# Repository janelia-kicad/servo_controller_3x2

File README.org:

# Created 2018-11-28 Wed 14:32
#+OPTIONS: title:nil author:nil email:nil toc:t |:t ^:nil
* Repository Information

- Name :: servo_controller_3x2
- Version :: 1.0
- License :: Open-Source Hardware
- URL :: https://github.com/janelia-kicad/servo_controller_3x2
- Author :: Peter Polidoro
- Email :: peter@polidoro.io

** Description

This device independently controls up to 16 5V hobby servos.

* Images

* Schematic

[[file:./schematic/servo_controller_3x2.pdf][./schematic/servo_controller_3x2.pdf]]

[[file:./schematic/images/schematic00.png]]

[[file:./schematic/images/schematic01.png]]

* Gerbers

Send gerbers zip file to your favorite PCB manufacturer for fabrication.

[[file:./gerbers/servo_controller_3x2_v1.0.zip][./gerbers/servo_controller_3x2_v1.0.zip]]

[[file:./gerbers/images/gerbers00.png]]

[[file:./gerbers/images/gerbers01.png]]

* Bill of Materials

** PCB Parts

| Item | Reference(s)    | Quantity | PartNumber        | Vendor  | Description                                              |
|------+-----------------+----------+-------------------+---------+----------------------------------------------------------|
|    1 | C1              |        1 | PCE3812CT-ND      | digikey | CAP ALUM 220UF 20% 50V SMD                               |
|    2 | C2              |        1 | 399-13229-1-ND    | digikey | CAP CER 0.1UF 50V 10% X7R 1210                           |
|    3 | C3              |        1 | 445-4536-1-ND     | digikey | CAP CER 10UF 50V 10% X7S 1210                            |
|    4 | D1              |        1 | 568-11697-1-ND    | digikey | DIODE SCHOTTKY 45V 10A CFP15                             |
|    5 | L1              |        1 | 350-1722-ND       | digikey | LED 2MM 5V VERTICAL RED PC MNT                           |
|    6 | MDB1            |        2 | S1011E-16-ND      | digikey | 16 Position Header Through Hole Male Pins                |
|    7 | P1              |        1 | CP-063AH-ND       | digikey | CONN PWR JACK DC 2.1X5.5 8A T/H                          |
|    8 | P2              |        1 | SAM12360-ND       | digikey | TSW-116-07-L-T                                           |
|    9 | R1 R2           |        2 | YAG5470CT-ND      | digikey | RES SMD 4.7K OHM 1% 1/2W 1210                            |
|   10 | RP1 RP2 RP3 RP4 |        4 | 744C083221JPCT-ND | digikey | RES ARRAY 4 RES 220 OHM 2012                             |
|   11 | U1              |        1 | 568-5931-1-ND     | digikey | LED Driver IC 16 Output Linear PWM Dimming 25mA 28-TSSOP |

** Supplemental Parts

| Item | Quantity | PartNumber   | Vendor  | Description                       |
|------+----------+--------------+---------+-----------------------------------|
|    1 |        1 | 1939-1410-ND | digikey | 40W 5V 8A DESKTOP                 |
|    2 |        1 | 1939-1027-ND | digikey | CORD 18AWG 1-15P - 320-C7 6FT BLK |
|    3 |        4 | 1738-1255-ND | digikey | 9G METAL GEAR MICRO SERVO         |
|      |          |              |         |                                   |

** Vendor Parts Lists

[[file:./bom/digikey_parts.csv][./bom/digikey_parts.csv]]

[[file:./bom/supplemental_digikey_parts.csv][./bom/supplemental_digikey_parts.csv]]

* Supplemental Documentation

** Assembly Instructions

- Solder surface mount and through hole components onto the pcb.

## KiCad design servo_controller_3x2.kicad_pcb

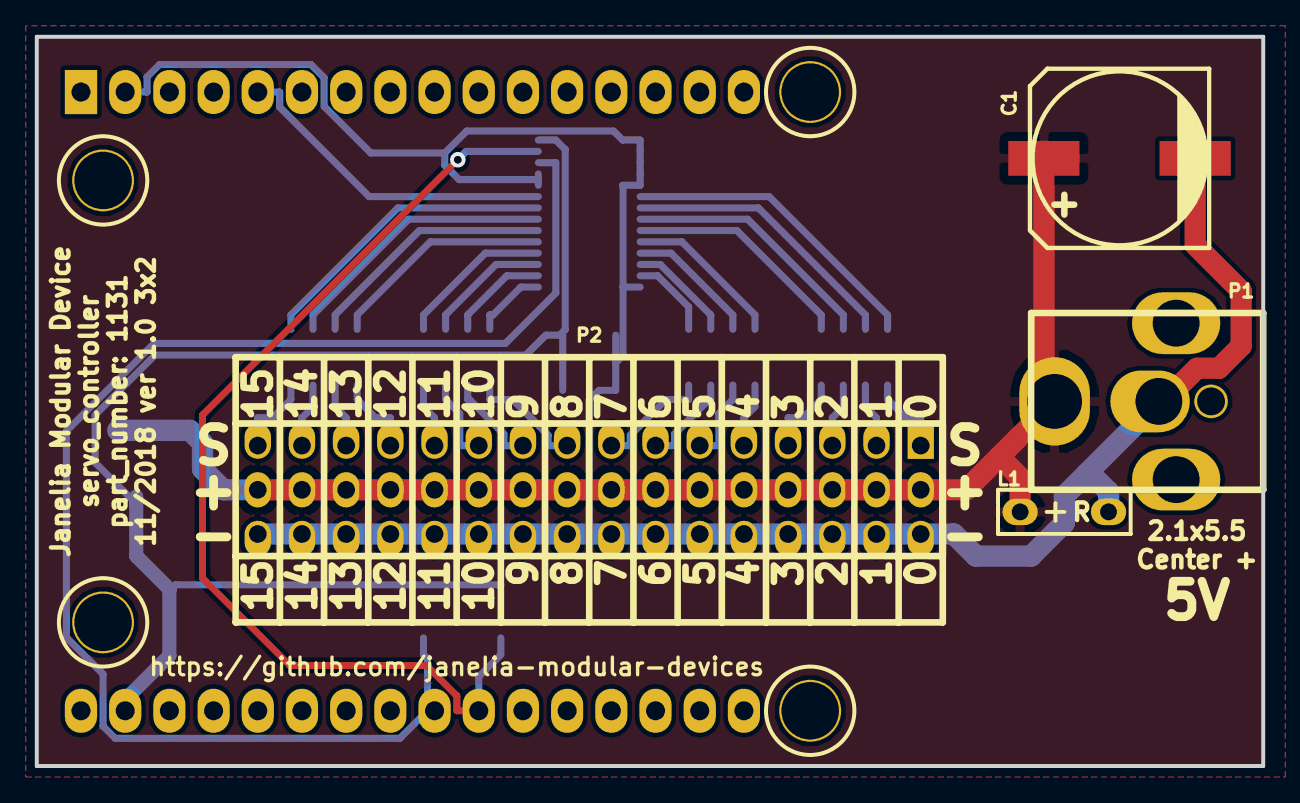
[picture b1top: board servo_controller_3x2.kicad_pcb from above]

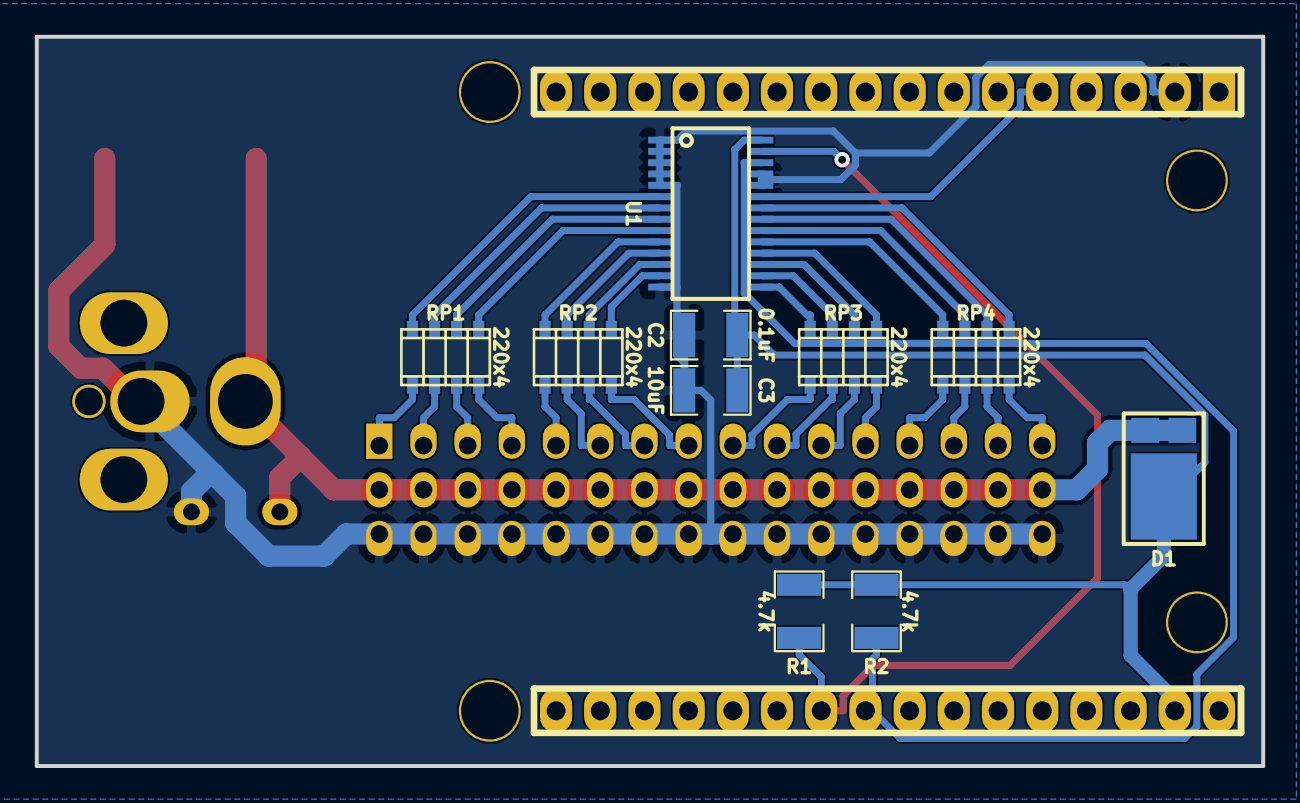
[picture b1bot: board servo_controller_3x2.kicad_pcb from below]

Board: 2 copper layers, 70.5 x 41.9 mm, 15 parts (10 on the bottom side), 38 nets.

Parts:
C1: 220uF_POL; C_ELEC_10
C2: 0.1uF; SM1210
C3: 10uF; SM1210
D1: diode_schottky_45V_10A; CFP15
L1: LED_5V_RED; LED_555-3XXX_R
MDB1: VAL**; MODULAR_DEVICE_BASE_3X2_MALE
P1: PWR_JACK_2.1x5.5; DCJACK_2PIN_HIGHCURRENT
P2: HEADER_03X16; HEADER_03x16
R1, R2: 4.7k; SM1210
RP1, RP2, RP3, RP4: 220x4; RESISTOR_PACK_SM1206x4
U1: PCA9685; TSSOP28

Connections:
/SCL: MDB1.19, R2.2, U1.26
/SDA: MDB1.18, R1.2, U1.27
/servo_3x2/PWM_0: RP1.7, U1.6
/servo_3x2/PWM_1: RP1.5, U1.7
/servo_3x2/PWM_2: RP1.3, U1.8
/servo_3x2/PWM_3: RP1.1, U1.9
/servo_3x2/PWM_4: RP2.7, U1.10
/servo_3x2/PWM_5: RP2.5, U1.11
/servo_3x2/PWM_6: RP2.3, U1.12
/servo_3x2/PWM_7: RP2.1, U1.13
/servo_3x2/PWM_8: RP3.7, U1.15
/servo_3x2/PWM_9: RP3.5, U1.16
/servo_3x2/PWM_10: RP3.3, U1.17
/servo_3x2/PWM_11: RP3.1, U1.18
/servo_3x2/PWM_12: RP4.7, U1.19
/servo_3x2/PWM_13: RP4.5, U1.20
/servo_3x2/PWM_14: RP4.3, U1.21
/servo_3x2/PWM_15: RP4.1, U1.22
/servo_3x2/SIG_0: P2.1, RP1.8
/servo_3x2/SIG_1: P2.4, RP1.6
/servo_3x2/SIG_2: P2.7, RP1.4
/servo_3x2/SIG_3: P2.10, RP1.2
/servo_3x2/SIG_4: P2.13, RP2.8
/servo_3x2/SIG_5: P2.16, RP2.6
/servo_3x2/SIG_6: P2.19, RP2.4
/servo_3x2/SIG_7: P2.22, RP2.2
/servo_3x2/SIG_8: P2.25, RP3.8
/servo_3x2/SIG_9: P2.28, RP3.6
/servo_3x2/SIG_10: P2.31, RP3.4
/servo_3x2/SIG_11: P2.34, RP3.2
/servo_3x2/SIG_12: P2.37, RP4.8
/servo_3x2/SIG_13: P2.40, RP4.6
/servo_3x2/SIG_14: P2.43, RP4.4
/servo_3x2/SIG_15: P2.46, RP4.2
/~ENABLE: MDB1.2, U1.23
GND: C1.2, C2.2, C3.2, L1.2, MDB1.GND, P1.2, P2.3, P2.6, P2.9, P2.12, P2.15, P2.18, P2.21, P2.24, P2.27, P2.30, P2.33, P2.36, P2.39, P2.42, P2.45, P2.48, U1.1, U1.2, U1.3, U1.4, U1.5, U1.14, U1.24, U1.25
VCC: C1.1, D1.2, L1.1, P1.1, P2.2, P2.5, P2.8, P2.11, P2.14, P2.17, P2.20, P2.23, P2.26, P2.29, P2.32, P2.35, P2.38, P2.41, P2.44, P2.47
VEE: C2.1, C3.1, D1.1, MDB1.VEE, R1.1, R2.1, U1.28

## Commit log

2018-11-26 Initial commit.
2018-11-26 Added generate_kicad_documentation submodule.
2018-11-26 Added components.
2018-11-27 Progress towards v1.0.
2018-11-27 Finished routing.
2018-11-28 Finished v1.0.
2018-11-28 Finished documentation v1.0.
2018-11-28 Updated images.
2018-11-28 Fixed image rotation.
2018-11-28 Updated submodules.
2021-09-16 Update email address
2021-09-21 Remove ignored files
2022-02-22 Add guix files
2022-02-23 Add guix documentation
